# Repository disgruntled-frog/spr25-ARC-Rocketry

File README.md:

# spr25-ARC-Rocketry
Repo to track:

  - [ ] KiCad Schematics, PCB designs
  - [ ] MCU Code
  - [ ] Base Station Code
  - [ ] TODO list (.md)
  - [ ] Obsidian Notes regarding research or plans (.md)
  - [ ] Any additional resources deemed helpful

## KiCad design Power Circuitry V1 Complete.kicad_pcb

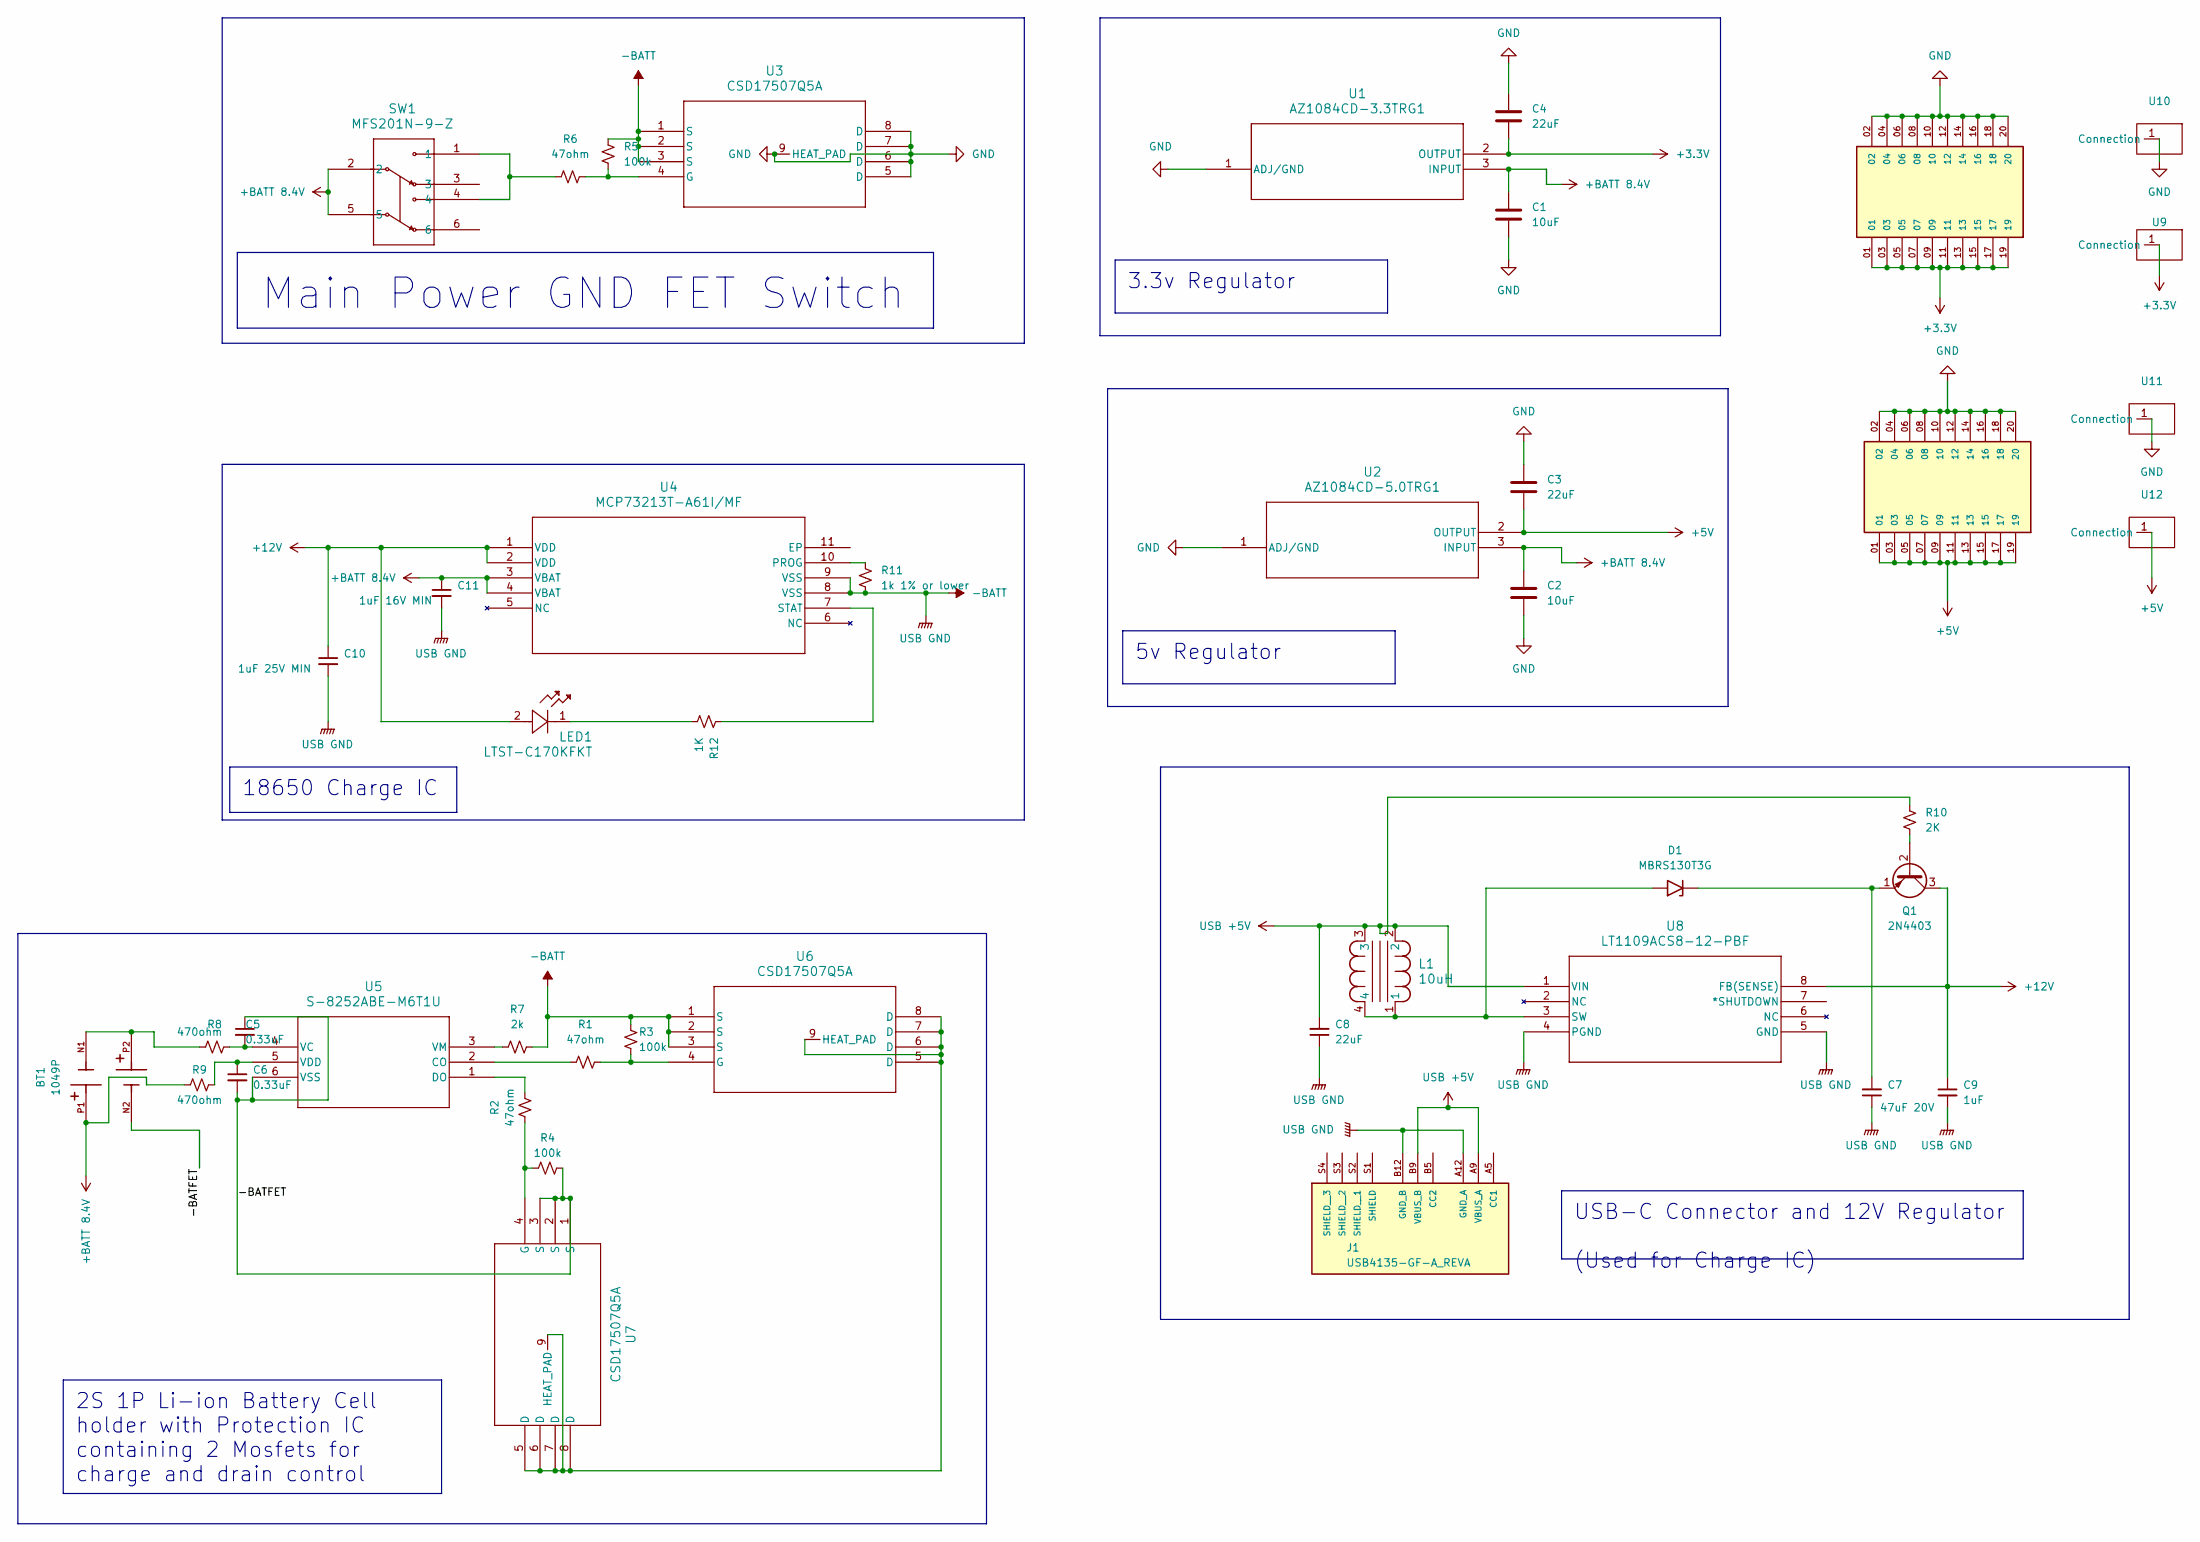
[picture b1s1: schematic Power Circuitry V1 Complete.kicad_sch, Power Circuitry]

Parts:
BT1: 1049P; BAT_1049P; PARTREV F
C1, C2: 10uF; C_0805_2012Metric_Pad1.18x1.45mm_HandSolder
C3, C4, C8: 22uF; C_1206_3216Metric_Pad1.33x1.80mm_HandSolder
C5, C6: 0.33uF; C_0402_1005Metric_Pad0.74x0.62mm_HandSolder
C7: 47uF 20V; C_1206_3216Metric_Pad1.33x1.80mm_HandSolder
C9: 1uF; C_0603_1608Metric_Pad1.08x0.95mm_HandSolder
C10: 1uF 25V MIN; C_0603_1608Metric_Pad1.08x0.95mm_HandSolder
C11: 1uF 16V MIN; C_0603_1608Metric_Pad1.08x0.95mm_HandSolder
D1: MBRS130T3G; D_SMB
J1: USB4135-GF-A_REVA; GCT_USB4135-GF-A_REVA; PARTREV A
J4, J5: SMS-110-X-X-D; SAMTEC_SMS-110-X-X-D; PARTREV 11-30-93
L1: 10uH; IND_CB_CTX-1
LED1: LTST-C170KFKT; LED_LTST-C170KFKT_LTO-M; LCSC # C284931
Q1: 2N4403; TO-92_Inline; LCSC # C258190
R1, R2, R6: 47ohm; R_0805_2012Metric_Pad1.20x1.40mm_HandSolder
R3, R4, R5: 100k; R_0805_2012Metric_Pad1.20x1.40mm_HandSolder
R7: 2k; R_0805_2012Metric_Pad1.20x1.40mm_HandSolder
R8, R9: 470ohm; R_0603_1608Metric_Pad0.98x0.95mm_HandSolder
R10: 2K; R_0805_2012Metric_Pad1.20x1.40mm_HandSolder
R11: 1k 1% or lower; R_0805_2012Metric_Pad1.20x1.40mm_HandSolder
R12: 1K; R_0805_2012Metric_Pad1.20x1.40mm_HandSolder
SW1: MFS201N-9-Z; MFS201N-9-Z_NDC
U1: AZ1084CD-3.3TRG1; LCSC # C151391
U2: AZ1084CD-5.0TRG1; LCSC # C2980701
U3, U7: CSD17507Q5A; LCSC # C2866779
U4: MCP73213T-A61I/MF; MCP73213T-A61I-MF; LCSC # C623835
U5: S-8252ABE-M6T1U; LCSC # C3682848
U6: CSD17507Q5A; LCSC # CSD17507Q5A
U8: LT1109ACS8-12-PBF; LT1109ACS8-12#PBF
U9, U10, U11, U12: Power_Pad 5mm x 10mm

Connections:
+3.3V: C4.2, J4.01, J4.03, J4.05, J4.07, J4.09, J4.11, J4.13, J4.15, J4.17, J4.19, U1.2 (OUTPUT), U9.1 (Connection)
+5V: C3.2, J5.01, J5.03, J5.05, J5.07, J5.09, J5.11, J5.13, J5.15, J5.17, J5.19, U2.2 (OUTPUT), U12.1 (Connection)
+12V: C9.1, C10.1, LED1.2, Q1.3 (C), U4.1 (VDD), U4.2 (VDD), U8.8 (FB(SENSE))
+BATT 8.4V: BT1.P1, C1.1, C2.1, C11.1, R9.1, SW1.2, SW1.5, U1.3 (INPUT), U2.3 (INPUT), U4.3 (VBAT), U4.4 (VBAT)
-BATT: C7.1, C8.1, C9.2, C10.2, C11.2, J1.A12 (GND_A), J1.B12 (GND_B), R3.1, R5.2, R7.2, R11.2, U3.1 (S), U3.2 (S), U3.3 (S), U4.8 (VSS), U4.9 (VSS), U6.1 (S), U6.2 (S), U6.3 (S), U8.4 (PGND), U8.5 (GND)
/-BATFET: BT1.N2, C5.1, C6.2, R4.2, U5.6 (VSS), U7.1 (S), U7.2 (S), U7.3 (S)
GND: C1.2, C2.2, C3.1, C4.1, J4.02, J4.04, J4.06, J4.08, J4.10, J4.12, J4.14, J4.16, J4.18, J4.20, J5.02, J5.04, J5.06, J5.08, J5.10, J5.12, J5.14, J5.16, J5.18, J5.20, U1.1 (ADJ/GND), U2.1 (ADJ/GND), U3.5 (D), U3.6 (D), U3.7 (D), U3.8 (D), U3.9 (HEAT_PAD), U10.1 (Connection), U11.1 (Connection)
unnamed: BT1.N1, BT1.P2, R8.1
unnamed: C7.2, D1.1 (A1), Q1.1 (E)
unnamed: D1.2 (A2), L1.1, L1.4, U8.3 (SW)
unnamed: LED1.1, R12.2
unnamed: Q1.2 (B), R10.1
unnamed: R6.1, SW1.1, SW1.4
unnamed: R5.1, R6.2, U3.4 (G)
unnamed: R11.1, U4.10 (PROG)
unnamed: R12.1, U4.7 (STAT)
unnamed: R1.2, U5.2 (CO)
unnamed: R2.1, U5.1 (DO)
unnamed: C5.2, R8.2, U5.4 (VC)
unnamed: C6.1, R9.2, U5.5 (VDD)
unnamed: R7.1, U5.3 (VM)
unnamed: R1.1, R3.2, U6.4 (G)
unnamed: U6.5 (D), U6.6 (D), U6.7 (D), U6.8 (D), U6.9 (HEAT_PAD), U7.5 (D), U7.6 (D), U7.7 (D), U7.8 (D), U7.9 (HEAT_PAD)
unnamed: R2.2, R4.1, U7.4 (G)
USB +5V: C8.2, J1.A9 (VBUS_A), J1.B9 (VBUS_B), L1.2, L1.3, R10.2, U8.1 (VIN)

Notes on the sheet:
3.3v Regulator
5v Regulator
18650 Charge IC
Main Power GND FET Switch
2S 1P Li-ion Battery Cell holder with Protection IC containing 2 Mosfets for charge and drain control
USB-C Connector and 12V Regulator (Used for Charge IC)

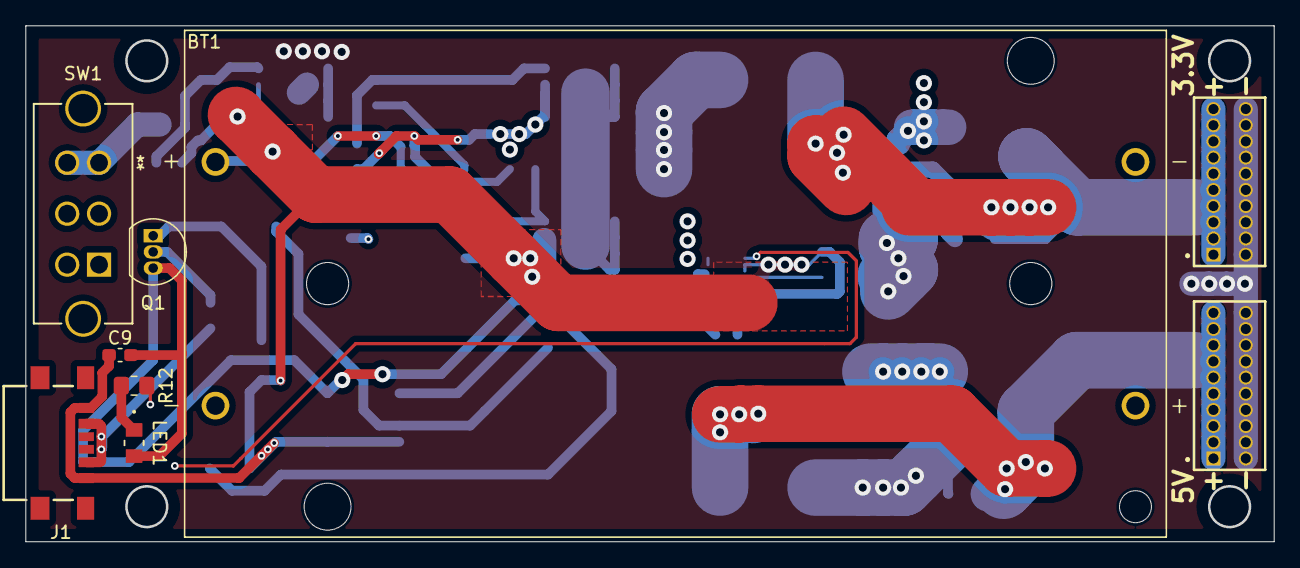
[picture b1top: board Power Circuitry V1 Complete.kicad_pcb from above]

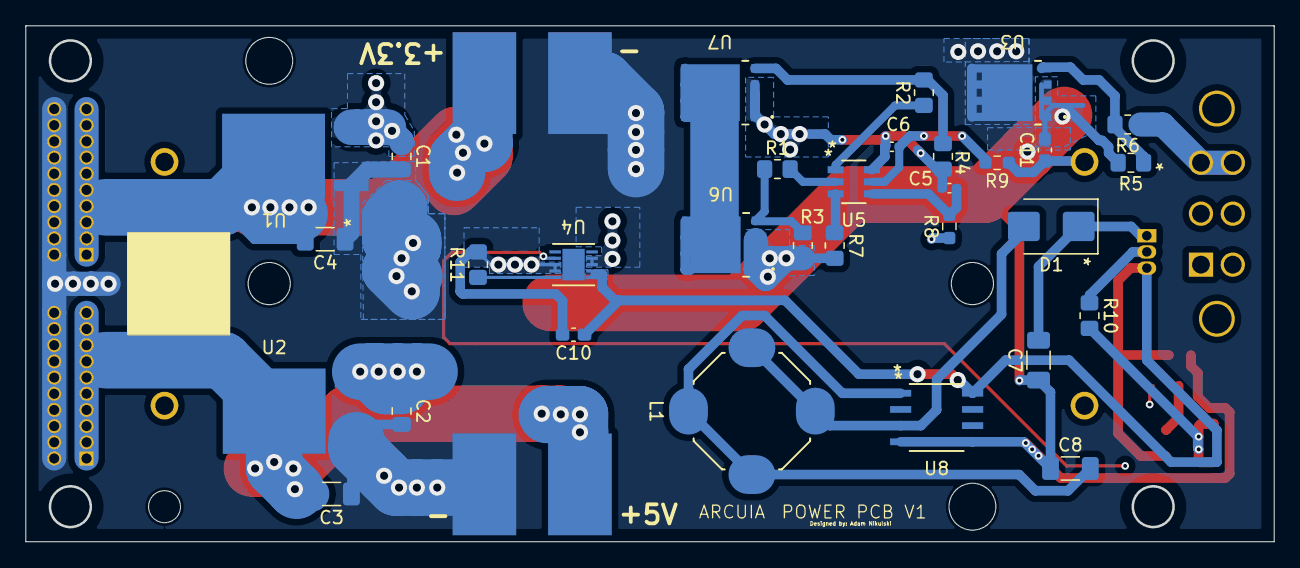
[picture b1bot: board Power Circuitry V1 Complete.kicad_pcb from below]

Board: 4 copper layers, 98.0 x 40.5 mm, 44 parts (35 on the bottom side), 25 nets.

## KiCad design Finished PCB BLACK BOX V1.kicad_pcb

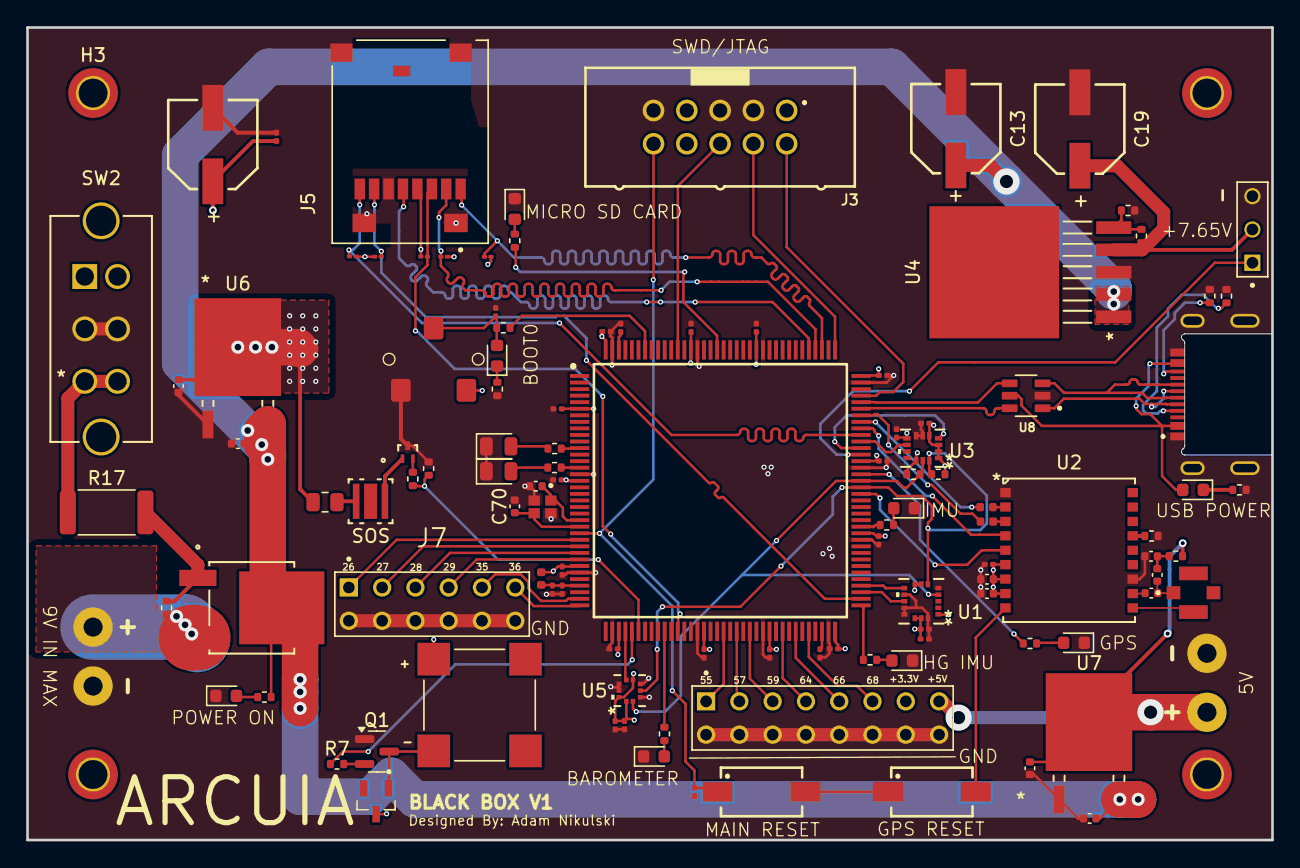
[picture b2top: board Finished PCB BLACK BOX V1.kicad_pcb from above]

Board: 4 copper layers, 95.0 x 62.0 mm, 116 parts (0 on the bottom side), 89 nets.

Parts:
C1, C3, C6, C21, C28, C36, C40, C67, C74, C75, C76, C77, C78, C79, C80, C81, C82, C83, C84, C85, C86, C87, C88: 100nF; C_0201_0603Metric
C2: 47pF; C_0402_1005Metric
C4: 1uF; C_0402_1005Metric
C5, C18, C31: 10uF; C_0402_1005Metric
C7: 4.7uF; C_0201_0603Metric
C13, C19: WCAP-HSG5_D6.3H5.8P2.2
C20: 10uF AL; C_0201_0603Metric
C27: 10nF; C_0402_1005Metric
C29, C30: 22uF; C_0402_1005Metric
C42: 10uF AL; WCAP-HSG5_D6.3H5.8P2.2
C70, C73: 4pF; C_0402_1005Metric
C71: 10uF; C_0201_0603Metric
C72: 1uF; C_0201_0603Metric
D1: BZX84-C12_215; SOT95P230X110-3N
D2: GREEN LED; LED_0603_1608Metric
D3: BLUE USB LED; LED_0603_1608Metric
D4: BIG BLUE LED; LED_0805_2012Metric
D5: WHITE BOOT LED; LED_0603_1608Metric
D6: PURPLE LED; LED_0805_2012Metric
D7: Light green SD CARD LED; LED_0603_1608Metric
D8: TEAL LED; LED_0603_1608Metric
D9: YELLOW LED; LED_0603_1608Metric
D10: Orange LED; LED_0603_1608Metric
D11: RED POWER LED; LED_0603_1608Metric
H1, H2, H3, H4: MountingHole_Pad_MP; MountingHole_2.2mm_M2_DIN965_Pad_TopBottom
IC3: STM32H573ZIT6
J1: 5-146285-3; TE_5-146285-3
J2: CNMHF1; LINX_CONMHF1-SMD-G-T
J3: 6120XX21621_61201021621; 61201021621
J4: GSB1C4621DS2HR; AMPHENOL_GSB1C4621DS2HR
J5: ST1W008S4TR2000; JAE_ST1W008S4TR2000
J6: 87215-5; TE_87215-5
J7: 87215-3; TE_87215-3
L1, L2, L7: BLM15HD102SN1D; L_0402_1005Metric
L3: 27nH; C_0402_1005Metric
LS1: CMT-8504-100-SMT-TR; XDCR_CMT-8504-100-SMT-TR
Q1: 2PD601BRL; SOT-23
Q2: VESM_TOS
R1, R2: 10 Ohm; R_0402_1005Metric
R3, R10, R18, R22: 10Kohm; R_0402_1005Metric
R4: 75Kohm; R_0402_1005Metric
R5, R15: 5.11Kohm; R_0402_1005Metric
R6, R14, R19, R29, R30: 47K Ohms; R_01005_0402Metric
R7, R9: 180ohm; R_0402_1005Metric
R8: 7.6 Ohms 0.25W; R_0805_2012Metric
R11, R12: 680ohms; R_0402_1005Metric
R13, R20, R23, R25: 1 Ohm; R_0402_1005Metric
R16: 1.5K Ohm; R_0402_1005Metric
R17: 100 ohm 1W or larger; R_2512_6332Metric
R21: 300 Ohm; R_0402_1005Metric
R24: 800 Ohm; R_0402_1005Metric
R26: 1K Ohm; R_0402_1005Metric
R27: 680 Ohms; R_0402_1005Metric
R28: 6.2K Ohms; R_0402_1005Metric
S2, S5: 434121043836
SOS: LJ CRBP.01-JZLX-27-3A4A-350-R18; LJ_CRBP_OSR
SW2: MFS201N-9-Z; MFS201N-9-Z_NDC
SW4: SW_SPDT_321; CL-SB-12B-02T
U1: H3LIS100DLTR; TFLGA16_3P15X3P15_STM-L
U2: MAX-M8W-0; SMT_M8W-0_UBL-L
U3: LSM6DSOTR; LGA-14L_2P5X3X0P86_STM-L
U4: NCV5662DSADJR4G; D2PAK-5_ONS
U5: LPS22HHTR; HLGA-10L_2X2X0P73_STM-L
U6: AZ1084CD-3.3TRG1; TO-252-3_6P6X6P1_DIO-L
U7: AZ1084CD-5.0TRG1; TO-252-3_6P6X6P1_DIO-L
U8: USBLC6-2SC6; SOT95P280X145-6N
U9: Battery terminal; BAT_16GA_THT_PAD
U10: FDD306P; TO252-3_369AS_FAS
Y5: ABM11W-48.0000MHZ-7-B1U-T3; XTAL_ABM11W-48.0000MHZ-7-B1U-T3

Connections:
2GPIO1: IC3.26 (PC0), J7.1
2GPIO2: IC3.27 (PC1), J7.2
2GPIO3: IC3.28 (PC2), J7.3
2GPIO4: IC3.29 (PC3), J7.4
2GPIO5: IC3.35 (PA1), J7.5
2GPIO6: IC3.36 (PA2), J7.6
+3.3V: C1.1, C3.2, C4.1, C5.1, C6.1, C7.1, C20.2, C21.2, C28.2, C29.1, C40.2, C42.2, C74.2, C75.2, C76.2, C77.2, C79.2, C80.2, C81.2, C82.2, C83.2, C85.2, C86.2, C87.2, C88.2, D1.3, IC3.6 (VBAT), IC3.17 (VDD_1), IC3.30 (VDD_2), IC3.39 (VDD_3), IC3.52 (VDD_4), IC3.62 (VDD_5), IC3.72 (VDD_6), IC3.84 (VDD_7), IC3.95 (VDD_8), IC3.108 (VDD_9), IC3.121 (VDDIO2), IC3.131 (VDD_10), IC3.144 (VDD_11), J3.1, J5.C4, J6.7, L7.2, LS1.P, R6.1, R8.2, R11.1, R12.1, R14.1, R19.1, R29.1, R30.1, SW4.3 (A), U1.1 (VDD_IO), U1.7 (SDO/SA0), U1.8 (CS), U1.14 (VDD), U1.15 (RESERVED), U2.6 (V_BCKP), U2.7 (VCC_IO), U2.8 (VCC), U3.1 (SDO/SA0), U3.2 (SDx), U3.3 (SCx), U3.5 (VDDIO), U3.8 (VDD), U3.12 (CS), U5.1 (VDD_IO), U5.6 (CS), U5.10 (VDD), U6.2 (OUTPUT)
+5V: C30.1, J6.8, R1.2, U7.2 (OUTPUT)
+7.65V: C19.2, J1.2, R4.2, U4.4 (VOUT)
+BATT: C13.2, C18.1, C31.1, R28.2, U4.1 (EN), U4.2 (VIN), U6.3 (INPUT), U7.3 (INPUT), U10.3
/+ BATT IN: R18.1, U9.1 (+), U10.2
/D+: J4.A6 (DP1), J4.B6 (DP2), U8.3
/D-: J4.A7 (DN1), J4.B7 (DN2), U8.1
BNO_INT1: IC3.97 (PC7), U3.4 (INT1)
BNO_INT2: IC3.98 (PC8), U3.9 (INT2)
BOOT0: IC3.138 (BOOT0), R22.1
Buzzer PWM: IC3.41 (PA5), R7.1
GND: C1.2, C3.1, C4.2, C5.2, C6.2, C7.2, C13.1, C18.2, C19.1, C20.1, C21.1, C27.1, C28.1, C29.2, C30.2, C31.2, C36.2, C40.1, C42.1, C67.2, C70.2, C71.1, C72.1, C73.1, C74.1, C75.1, C76.1, C77.1, C78.1, C79.1, C80.1, C81.1, C82.1, C83.1, C84.1, C85.1, C86.1, C87.1, C88.1, D2.1 (K), D4.1 (K), D6.1 (K), D7.1 (K), D8.1 (K), D9.1 (K), D10.1 (K), D11.1 (K), IC3.16 (VSS_1), IC3.31 (VSSA), IC3.38 (VSS_2), IC3.51 (VSS_3), IC3.61 (VSS_4), IC3.71 (VSS_5), IC3.83 (VSS_6), IC3.94 (VSS_7), IC3.107 (VSS_8), IC3.120 (VSS_9), IC3.130 (VSS_10), IC3.143 (VSS_11), J1.3, J3.3, J3.5, J3.9, J4.A1_B12 (GND_A), J4.B1_A12 (GND_B), J4.SH1 (SHIELD), J4.SH2 (SHIELD), J4.SH3 (SHIELD), J4.SH4 (SHIELD), J5.C6, J5.GND1 (GND), J5.GND2 (GND__1), J5.GND3 (GND__2), J5.GND4 (GND__3), J6.9, J6.10, J6.11, J6.12, J6.13, J6.14, J6.15, J6.16, J7.7, J7.8, J7.9, J7.10, J7.11, J7.12, Q1.1 (E), Q2.3 (S), R2.2, R3.1, R5.1, R10.1, R15.2, R16.1, R21.2, S2.1, S5.2, SW2.2, SW2.5, SW4.1 (C), U1.5 (GND), U1.10 (RESERVED), U1.12 (GND), U1.13 (GND), U1.16 (GND), U2.1 (GND), U2.12 (GND), U3.6 (GND), U3.7 (GND), U4.3 (GND), U5.3 (RES), U5.5 (SDO/SA0), U5.8 (GND), U5.9 (GND), U6.1 (ADJ/GND), U7.1 (ADJ/GND), U8.2, U9.2 (-), Y5.2 (GND), Y5.4 (GND)
GPIO 1: IC3.55 (PF15), J6.1
GPIO 2: IC3.57 (PG1), J6.2
GPIO 3: IC3.59 (PE8), J6.3
GPIO 4: IC3.64 (PE11), J6.4
GPIO 5: IC3.66 (PE13), J6.5
GPIO 6: IC3.68 (PE15), J6.6
GPS LED: IC3.93 (PG8), R13.1
H3_INT1: IC3.75 (PB14), U1.11 (INT1)
H3_INT2: IC3.76 (PB15), U1.9 (INT2)
I2C4_SCL: IC3.92 (PG7), R12.2, U1.4 (SCL/SPC), U3.13 (SCL), U5.2 (SCL/SPC)
I2C4_SDA: IC3.91 (PG6), R11.2, U1.6 (SDA/SDI/SDO), U3.14 (SDA), U5.4 (SDA/SDI/SDO)
LPS_INT1: IC3.40 (PA4), U5.7 (INT_DRDY)
Light Green LED: IC3.127 (PG12), R24.2
MAX_INT1: IC3.90 (PG5), U2.5 (EXINT)
MAX_Timepulse: IC3.100 (PA8), U2.4 (TIMEPULSE)
NRST: C67.1, IC3.25 (NRST), J3.10, S5.1
unnamed: C2.2, J2.1, L3.2
unnamed: C27.2, L3.1, R1.1
unnamed: D2.2 (A), R13.2
unnamed: D3.2 (A), J4.A4_B9 (VBUS_A), J4.B4_A9 (VBUS_B), U8.5
unnamed: D3.1 (K), R16.2
unnamed: D4.2 (A), R23.1
unnamed: C36.1, D5.2 (A), R22.2, SW4.2 (B)
unnamed: D5.1 (K), R21.1
unnamed: D6.2 (A), R20.1
unnamed: D7.2 (A), R24.1
unnamed: D8.2 (A), R25.1
unnamed: D9.2 (A), R26.1
unnamed: D10.2 (A), R27.1
unnamed: D11.2 (A), R28.1
unnamed: IC3.12 (PF2), R20.2
unnamed: IC3.15 (PF5), R23.2
unnamed: C73.2, IC3.23 (PH0-OSC_IN), Y5.1
unnamed: C70.1, IC3.24 (PH1-OSC_OUT), Y5.3
unnamed: C84.2, IC3.70 (VCAP_1)
unnamed: C78.2, IC3.142 (VCAP_2)
unnamed: C71.2, C72.2, IC3.33 (VDDA), L7.1
unnamed: J2.S1, U2.10 (GND)
unnamed: J4.A5 (CC1), R5.2
unnamed: J4.B5 (CC2), R15.1
unnamed: R8.1, SOS.2
unnamed: Q1.2 (B), R7.2
unnamed: D1.1, LS1.N, Q1.3 (C)
unnamed: Q2.1 (D), SOS.1
unnamed: Q2.2 (G), R9.1
unnamed: R17.1, SW2.1, SW2.4
unnamed: R17.2, R18.2, U10.1
unnamed: S2.2, U2.9 (RESET_N)
unnamed: C2.1, U2.11 (RF_IN)
unnamed: L1.1, U2.3 (RxD)
unnamed: L2.1, U2.2 (TxD)
unnamed: R2.1, U2.15 (V_ANT)
unnamed: R3.2, R4.1, U4.5 (ADJ)
Orange LED: IC3.46 (PB0), R27.2
Rx: IC3.102 (PA10), L1.2
SDIO_CLK: IC3.113 (PC12), J5.C5
SDIO_CMD: IC3.48 (PB2), J5.C3, R19.2
SDIO_D0: IC3.74 (PB13), J5.C7, R29.2
SDIO_D1: IC3.99 (PC9), J5.C8, R30.2
SDIO_D2: IC3.111 (PC10), J5.C1, R6.2
SDIO_D3: IC3.112 (PC11), J5.C2, R14.2
SERVO SIGNAL: IC3.96 (PC6), J1.1
SOS PWM: IC3.42 (PA6), R9.2, R10.2
SWCLK: IC3.109 (PA14), J3.4
SWDIO: IC3.105 (PA13), J3.2
SWO: IC3.133 (PB3), J3.6
TEAL IMU LED: IC3.85 (PD14), R25.2
Tx: IC3.101 (PA9), L2.2
USB_DATA_OUT +: IC3.104 (PA12), U8.4
USB_DATA_OUT -: IC3.103 (PA11), U8.6
Yellow LED: IC3.73 (PB12), R26.2

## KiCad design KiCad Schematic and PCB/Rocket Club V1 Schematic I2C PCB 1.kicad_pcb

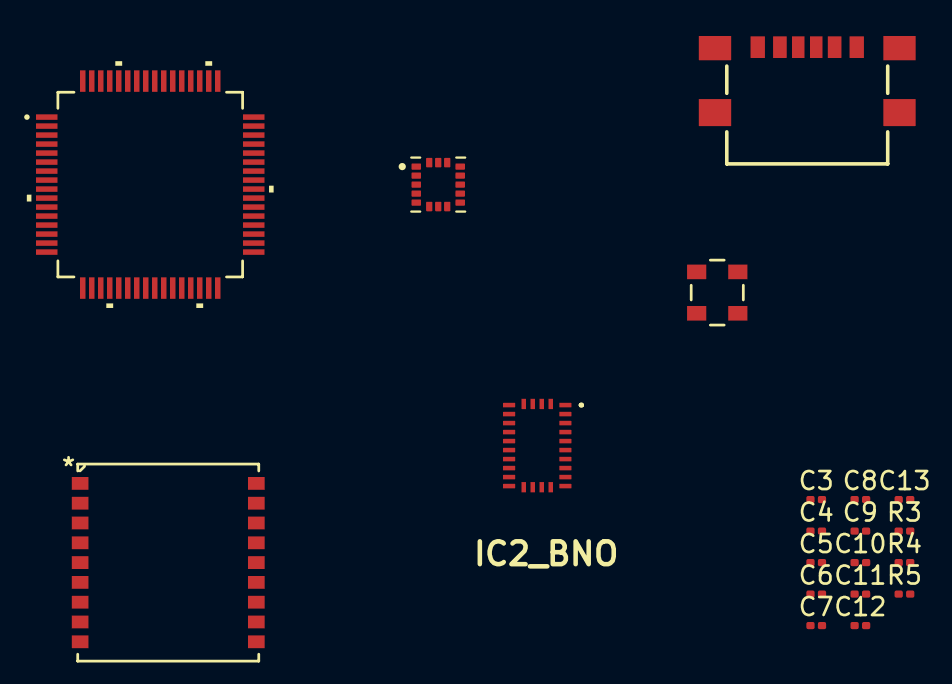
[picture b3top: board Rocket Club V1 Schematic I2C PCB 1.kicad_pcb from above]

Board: 2 copper layers, 20 parts (0 on the bottom side), 16 nets, no tracks yet.

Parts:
C3, C4, C5, C6, C7, C8, C9, C10, C11, C12, C13: C; C_0201_0603Metric
IC1: STM32H573RIT6; LQFP64-10x10mm_STM
IC2_BNO: BNO085
J1: USB4135-GF-A_REVA; GCT_USB4135-GF-A_REVA
Oscillator 3.3V 16MHz1: Oscillator 3.3V 16MHz; SMT_16.000000_TTN
R3, R4, R5: R; R_0201_0603Metric
U1: H3LIS100DLTR; PQFN50P300X300X100-16N-H3
U3: MAX-M8W-0; SMT_M8W-0_UBL

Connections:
3.3V: C3.2, C4.2, C5.2, C6.1, C7.1, C8.2, C9.2, C10.2, C11.2, C12.2, IC1.13 (VDDA), IC1.19 (VDD_1), IC1.32 (VDD_2), IC1.48 (VDD_3), IC1.64 (VDD_4), IC2_BNO.3 (VDD), IC2_BNO.5 (PS1), IC2_BNO.17 (SA0/H_MOSI_), IC2_BNO.28 (VDDIO), Oscillator 3.3V 16MHz1.1 (VCTCXO), Oscillator 3.3V 16MHz1.4 (VDD), R3.1, R4.1, R5.1, U1.1 (VDD_IO), U1.8 (CS), U1.14 (VDD), U3.7, U3.8
BNO_INT1: IC1.36 (PB15), IC2_BNO.14 (H_INTN)
GND: C3.1, C4.1, C5.1, C6.2, C7.2, C8.1, C9.1, C10.1, C11.1, C12.1, C13.1, IC1.12 (VSSA), IC1.18 (VSS_1), IC1.31 (VSS_2), IC1.47 (VSS_3), IC1.63 (VSS_4), IC2_BNO.2 (GND_1), IC2_BNO.4 (BOOTN), IC2_BNO.6 (PS0/WAKE), IC2_BNO.25 (GND_2), J1.A12 (GND_A), J1.B12 (GND_B), Oscillator 3.3V 16MHz1.2 (GND), U1.5 (GND), U1.7 (SDO/SA0), U1.10 (RESERVED), U1.12 (GND), U1.13 (GND), U1.15 (RESERVED), U1.16 (GND), U3.1, U3.10, U3.12
H3_INT1: IC1.34 (PB13), U1.11 (INT1)
H3_INT2: IC1.33 (PB12), U1.9 (INT2)
I2C1_SCL: IC1.61 (PB8), IC2_BNO.19 (H_SCL/SCK/RX), R4.2, U1.4 (SCL/SPC), U3.17
I2C1_SDA: IC1.59 (PB7), IC2_BNO.20 (H_SDA/H_MISO/TX_), R5.2, U1.6 (SDA/SDI/SDO), U3.16
MAX_INT1: IC1.39 (PC8), U3.5
MAX_Reset: IC1.40 (PC9), U3.9
MAX_Timepulse_INT2: IC1.41 (PA8), U3.4
MAX_USART2_RX: IC1.15 (PA1), U3.2
MAX_USART2_TX: IC1.14 (PA0), U3.3
NRST: IC1.7 (NRST), IC2_BNO.11 (NRST)
unnamed: IC1.5 (PH0-OSC_IN), Oscillator 3.3V 16MHz1.3 (Output)
unnamed: C13.2, IC2_BNO.9 (CAP)
unnamed: IC2_BNO.10 (CLKSEL0), R3.2

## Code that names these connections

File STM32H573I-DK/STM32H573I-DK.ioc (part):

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Mcu.Name=STM32H573IIKxQ
Mcu.Package=UFBGA176
Mcu.UserName=STM32H573IIKxQ
PA0.GPIOParameters=GPIO_Label
PA0.GPIO_Label=ARD_A2
PA0.Signal=ADCx_INP0
PA1.GPIOParameters=GPIO_Label
PA1.GPIO_Label=RMII_REF_CLK
PA1.Signal=ETH_REF_CLK
PA10.Signal=USART1_RX
PA11.GPIOParameters=GPIO_Label
PA11.GPIO_Label=USB_FS_N
PA11.Signal=USB_DM
PA12.GPIOParameters=GPIO_Label
PA12.GPIO_Label=USB_FS_P
PA12.Signal=USB_DP
PA13(JTMS/SWDIO).GPIOParameters=GPIO_Label
PA13(JTMS/SWDIO).GPIO_Label=JTMS
PA13(JTMS/SWDIO).Signal=DEBUG_JTMS-SWDIO
PA14(JTCK/SWCLK).GPIOParameters=GPIO_Label
PA14(JTCK/SWCLK).GPIO_Label=JTCK
PA14(JTCK/SWCLK).Signal=DEBUG_JTCK-SWCLK
PA15(JTDI).GPIOParameters=GPIO_Label
PA15(JTDI).GPIO_Label=JTDI
PA15(JTDI).Signal=DEBUG_JTDI
PA2.GPIOParameters=GPIO_Label
PA2.GPIO_Label=RMII_MDIO
PA2.Signal=ETH_MDIO
PA3.GPIOParameters=GPIO_Label
PA3.GPIO_Label=ARD_D10
PA3.Signal=SPI2_NSS
PA4.GPIOParameters=GPIO_Label
PA4.GPIO_Label=ARD_A1
PA4.Signal=ADCx_INP18
PA5.GPIOParameters=GPIO_Label
PA5.GPIO_Label=ARD_A3
PA5.Signal=ADCx_INP19
PA6.GPIOParameters=GPIO_Label
PA6.GPIO_Label=ARD_A4
PA6.Signal=ADCx_INP3
PA7.GPIOParameters=GPIO_Label
PA7.GPIO_Label=RMII_CRS_DV
PA7.Signal=ETH_CRS_DV
PA8.GPIOParameters=GPIO_Label
PA8.GPIO_Label=ARD_D9
PA8.Signal=S_TIM1_CH1
PA9.Signal=USART1_TX
PB0.GPIOParameters=GPIO_Label
PB0.GPIO_Label=ARD_A0
PB0.Signal=ADCx_INP9
PB1.Signal=OCTOSPI1_IO0
PB10.GPIOParameters=GPIO_Label
PB10.GPIO_Label=ARD_D1
PB10.Signal=USART3_TX
PB11.GPIOParameters=GPIO_Label
PB11.GPIO_Label=ARD_D0
PB11.Signal=USART3_RX
PB12.GPIOParameters=GPIO_Label
PB12.GPIO_Label=STMOD\#18
PB12.Signal=GPXTI12
PB13.GPIOParameters=GPIO_Label
PB13.GPIO_Label=UCPD_CC1
PB13.Signal=UCPD1_CC1
PB14.GPIOParameters=GPIO_Label
PB14.GPIO_Label=UCPD_CC2
PB14.Signal=UCPD1_CC2
PB15.GPIOParameters=GPIO_Label
PB15.GPIO_Label=ARD_D11
PB15.Signal=SPI2_MOSI
PB2.Signal=OCTOSPI1_DQS
PB3(JTDO/TRACESWO).GPIOParameters=GPIO_Label
PB3(JTDO/TRACESWO).GPIO_Label=SWO
PB3(JTDO/TRACESWO).Signal=DEBUG_JTDO-SWO
PB4(NJTRST).GPIOParameters=GPIO_Label
PB4(NJTRST).GPIO_Label=NJTRST
PB4(NJTRST).Signal=DEBUG_JTRST
PB5.GPIOParameters=GPIO_Label
PB5.GPIO_Label=ARD_D3
PB5.Signal=S_TIM3_CH2
PB6.GPIOParameters=GPIO_Label
PB6.GPIO_Label=I2C1_SCL
PB6.Mode=I2C
PB6.Signal=I2C1_SCL
PB7.GPIOParameters=GPIO_Label
PB7.GPIO_Label=I2C1_SDA
PB7.Mode=I2C
PB7.Signal=I2C1_SDA
PC0.Signal=OCTOSPI1_IO7
PC1.GPIOParameters=GPIO_Label
PC1.GPIO_Label=RMII_MDC
PC1.Signal=ETH_MDC
PC10.Signal=SDMMC1_D2
PC11.Signal=SDMMC1_D3
PC12.Signal=SDMMC1_CK
PC13.Signal=GPXTI13
PC14-OSC32_IN(OSC32_IN).Signal=RCC_OSC32_IN
PC15-OSC32_OUT(OSC32_OUT).Signal=RCC_OSC32_OUT
PC2.Signal=OCTOSPI1_IO2
PC3.GPIOParameters=GPIO_Label
PC3.GPIO_Label=PDM_SAI1_SD3
PC3.Signal=SAI1_D3
PC4.GPIOParameters=GPIO_Label
PC4.GPIO_Label=RMII_RXD0
PC4.Signal=ETH_RXD0
PC5.GPIOParameters=GPIO_Label
PC5.GPIO_Label=RMII_RXD1
PC5.Signal=ETH_RXD1
PC6.Signal=GPIO_Output
PC7.Signal=FMC_NE1
PC8.Signal=SDMMC1_D0
PC9.Signal=SDMMC1_D1
PD0.Signal=FMC_D2_DA2
PD1.Signal=FMC_D3_DA3
PD10.Signal=FMC_D15_DA15
PD11.Signal=SAI1_CK1
PD12.Signal=OCTOSPI1_IO1
PD13.Signal=OCTOSPI1_IO3
PD14.Signal=FMC_D0_DA0
PD15.Signal=FMC_D1_DA1
PD2.Signal=SDMMC1_CMD
PD3.Signal=FMC_CLK
PD4.Signal=FMC_NOE
PD5.Signal=FMC_NWE
PD6.Signal=SAI1_SD_A
PD8.Signal=FMC_D13_DA13
PD9.Signal=FMC_D14_DA14
PE0.GPIOParameters=GPIO_Label
PE0.GPIO_Label=DETECTN
PE0.Signal=GPIO_Output
PE1.GPIOParameters=GPIO_Label
PE1.GPIO_Label=MEMS_LED
PE1.Signal=GPIO_Output
PE10.Signal=FMC_D7_DA7
PE11.Signal=FMC_D8_DA8
PE12.Signal=FMC_D9_DA9
PE13.Signal=FMC_D10_DA10
PE14.Signal=FMC_D11_DA11
PE15.Signal=FMC_D12_DA12
PE2.Signal=DEBUG_TRACECLK
PE3.GPIOParameters=GPIO_Label
PE3.GPIO_Label=TRACED0
PE3.Signal=DEBUG_TRACED0
PE4.Signal=SAI1_D2
PE5.GPIOParameters=GPIO_Label
PE5.GPIO_Label=TRACED2
PE5.Signal=DEBUG_TRACED2
PE6.GPIOParameters=GPIO_Label
PE6.GPIO_Label=TRACED3
PE6.Signal=DEBUG_TRACED3
PE7.Signal=FMC_D4_DA4
PE8.Signal=FMC_D5_DA5
PE9.Signal=FMC_D6_DA6
PF0.Signal=FMC_A0
PF1.Signal=GPIO_Output
PF10.Signal=OCTOSPI1_CLK
PF11.GPIOParameters=GPIO_Label
PF11.GPIO_Label=STMOD\#13
PF11.Signal=ADC1_INP2
PF12.GPIOParameters=GPIO_Label
PF12.GPIO_Label=ARD_A5
PF12.Signal=ADC1_INP6
PF13.GPIOParameters=GPIO_Label
PF13.GPIO_Label=IBUS_SENSE
PF13.Signal=ADC2_INP2
PF14.GPIOParameters=GPIO_Label
PF14.GPIO_Label=VBUS_SENSE
PF14.Signal=ADC2_INP6
PF3.GPIOParameters=GPIO_Label
PF3.GPIO_Label=STMOD\#17
PF3.Signal=GPIO_Output
PF4.Signal=GPIO_Output
PG0.GPIOParameters=GPIO_Label
PG0.GPIO_Label=UCPD_PWR
PG0.Signal=GPIO_Output
PG1.GPIOParameters=GPIO_Label
PG1.GPIO_Label=UCPD_FLT
PG1.Signal=GPXTI1
PG10.GPIOParameters=GPIO_Label
PG10.GPIO_Label=SAI2_SD_B
PG10.Signal=SAI2_SD_B
PG11.GPIOParameters=GPIO_Label
PG11.GPIO_Label=RMII_TX_EN
PG11.Signal=ETH_TX_EN
PG12.GPIOParameters=GPIO_Label
PG12.GPIO_Label=RMII_TXD1
PG12.Signal=ETH_TXD1
PG13.Signal=ETH_TXD0
PG14.GPIOParameters=GPIO_Label
PG14.GPIO_Label=TRACED1
PG14.Signal=DEBUG_TRACED1
PG15.GPIOParameters=GPIO_Label
PG15.GPIO_Label=ARD_D2
PG15.Signal=GPIO_Output
PG3.GPIOParameters=GPIO_Label
PG3.GPIO_Label=LCD_CTP_RST
PG3.Signal=GPIO_Output
PG4.GPIOParameters=GPIO_Label
PG4.GPIO_Label=ARD_D4
PG4.Signal=GPIO_Output
PG5.GPIOParameters=GPIO_Label
PG5.GPIO_Label=ARD_D7
PG5.Signal=GPIO_Output
PG6.Signal=OCTOSPI1_NCS
PG7.Signal=GPXTI7
PG8.GPIOParameters=GPIO_Label
PG8.GPIO_Label=ARD_D8
PG8.Signal=GPIO_Output
PG9.Signal=OCTOSPI1_IO6
PH0-OSC_IN(PH0).Mode=HSE-DIG-External-Clock-Source
PH0-OSC_IN(PH0).Signal=RCC_OSC_IN
PH10.GPIOParameters=GPIO_Label
PH10.GPIO_Label=ARD_D6
PH10.Signal=S_TIM5_CH1
PH11.GPIOParameters=GPIO_Label
PH11.GPIO_Label=ARD_D5
PH11.Signal=S_TIM5_CH2
PH12.GPIOParameters=GPIO_Label
PH12.GPIO_Label=STMOD\#14-PWM
PH12.Signal=GPIO_Output
PH13.Signal=GPIO_Output
PH14.Signal=GPXTI14
PH2.Signal=OCTOSPI1_IO4
PH3.Signal=OCTOSPI1_IO5
PH4.GPIOParameters=GPIO_Label
PH4.GPIO_Label=STMOD\#19
PH4.Signal=GPIO_Output
PH5.GPIOParameters=GPIO_Label
PH5.GPIO_Label=STMOD\#20
PH5.Signal=GPIO_Output
PH6.GPIOParameters=GPIO_Label
PH6.GPIO_Label=STMOD\#12
PH6.Signal=GPIO_Output
PH7.GPIOParameters=GPIO_Label
PH7.GPIO_Label=STMOD\#12-RST
PH7.Signal=SPI5_MISO
PH8.GPIOParameters=GPIO_Label
PH8.GPIO_Label=STMOD\#9-MISOs
PH8.Signal=SPI5_MOSI
PH9.GPIOParameters=GPIO_Label
PH9.GPIO_Label=STMOD\#11-INT
PH9.Signal=GPIO_Output
PI1.GPIOParameters=GPIO_Label
PI1.GPIO_Label=ARD_D13
PI1.Signal=SPI2_SCK
PI10.GPIOParameters=GPIO_Label
PI10.GPIO_Label=RMII_RX_ER
PI10.Signal=ETH_RX_ER
PI11.Signal=GPIO_Output
PI2.GPIOParameters=GPIO_Label
PI2.GPIO_Label=ARD_D12
PI2.Signal=SPI2_MISO
PI3.Signal=GPIO_Output
PI4.Signal=SAI2_MCLK_A
PI5.Signal=SAI2_SCK_A
PI6.Signal=SAI2_SD_A
PI7.Signal=SAI2_FS_A
PI8.Signal=GPIO_Output
PI9.Signal=GPIO_Output
RCC.HSE_VALUE=25000000
RCC.SYSCLKFreq_VALUE=250000000
RCC.SYSCLKSource=RCC_SYSCLKSOURCE_PLLCLK
board=STM32H573I-DK
boardIOC=true

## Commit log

2025-02-09 vault backup: 2025-02-09 02:49:31
2025-02-09 vault backup: 2025-02-09 16:28:38
2025-02-09 vault backup: 2025-02-09 16:30:31
2025-02-11 Power Circuitry Schematic and Partially wired PCB
2025-02-16 Revert "Add files via upload"
    This reverts commit 12a37e3eec374fe353a4e50a20b182ffff322ece.
2025-02-19 vault backup: 2025-02-19 12:46:50
2025-02-19 vault backup: 2025-02-19 12:51:52
2025-02-25 Majority of Schematics
    It does NOT include radio (modem).
    STM32 only PARTIAL COMPLETE.
2025-02-25 Should have most schematics
    STM not done
    Doesn't have Radio (Modem)
2025-02-27 All Parts on Excel EXCEPT MODEM
    Full STM32H573RIT6
2025-02-28 Initial Commit. Dev Kit code, no user generated code at this stage.
2025-03-01 Start of a full Schematic
    VDD/VCC, VSS, SDA, SCL, mostly Labeled
2025-03-03 Test
2025-03-03 Datasheets
2025-03-03 LSM fully wired
2025-03-03 Both IMU's, BARO, and NOR(?) Completed
2025-03-05 Most Updated Sketch
2025-03-05 Includes MAX-M8W-0
2025-03-05 MAX-M8 Datasheet
2025-03-05 STM32 best datasheet
    The one on excel isn't right
2025-03-05 Made Sure all labels have an in and an out
    Should be labeled to my best extent
2025-03-13 Most Updated
2025-03-17 Most updated 3/17
2025-03-22 KiCad Footprints
2025-03-22 KiCad Schematic and PCB
2025-03-26 3/26/25
    Added NAND and labeled
2025-03-27 Footprints most updated
2025-03-27 Most Updated Footprints
2025-03-29 vault backup: 2025-03-29 12:40:33
2025-03-29 Includes Newest NAND Chip MT29
2025-03-31 Updated schematic, not fully done but majority done
2025-04-01 i dont know, just cuz
2025-04-02 i dont know, just cuz, pt.2 electric boogaloo
2025-04-04 4/4/25
2025-04-05 Number 8 again (was in wrong format)
2025-04-06 99% Done Schematic
2025-04-07 Finished schematic, will do a once over when I have more time
2025-04-10 With new STM ZIT6
2025-04-10 STM32 ZIT6 Footprint
2025-04-21 Finished PCB BLACK BOX V1
2025-10-11 LORA Basic Communication Code
2025-10-11 Create RYLR998
2025-10-11 Create
2025-10-11 LORA Basic communication
    Working on wirelessly sending data to OLED Screen
2025-10-21 Able to Transmit GPS data and Display on LCD
    Still need to add if statement for if Lat>0 transmit
